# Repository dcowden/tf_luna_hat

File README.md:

# This is a hat for an orange pi 5, v1.2, that exposes the uarts and can bus from the headers.

## Setting up the orange pi image

These high level steps are needed:

* Install arm overlays to enable uart 3 and 4
* disable serial gettys on the tty ports for these
* install i2c tools

## unpolished stuff I did
sudo apt update
sudo apt install -y \
  make build-essential libssl-dev zlib1g-dev \
  libbz2-dev libreadline-dev libsqlite3-dev \
  wget curl llvm libncurses5-dev libncursesw5-dev \
  xz-utils tk-dev libffi-dev liblzma-dev python3-pip git

# Install pyenv
curl https://pyenv.run | bash

# Add pyenv to your shell
echo 'export PATH="$HOME/.pyenv/bin:$PATH"' >> ~/.bashrc
echo 'eval "$(pyenv init -)"' >> ~/.bashrc
echo 'eval "$(pyenv virtualenv-init -)"' >> ~/.bashrc
source ~/.bashrc

# Install a specific Python version, e.g. 3.11.9
pyenv install 3.11.9

# Set it as the default for your user
pyenv global 3.11.9

# Verify
python --version
apt install i2c-tools

for b in 0 1 2 3 4 5 6 7 9 10; do echo "=== /dev/i2c-$b ==="; i2cdetect -y $b; done

pyenv virtualenv 3.11.9 i2c
pyenv activate
pyenv install smbus2

sudo usermod -aG i2c $USER
echo 'KERNEL=="i2c-[0-9]*", GROUP="i2c", MODE="0660"' | sudo tee /etc/udev/rules.d/99-i2c.rules
sudo udevadm control --reload-rules
sudo udevadm trigger
newgrp i2c

systemctl status serial-getty@ttyS4.service
# disable if active:
sudo systemctl disable --now serial-getty@ttyS4.service
sudo systemctl mask serial-getty@ttyS4.service
systemctl status serial-getty@ttyS4.service
# disable if active:
sudo systemctl disable --now serial-getty@ttyS3.service
sudo systemctl mask serial-getty@ttyS3.service

u-boot-update

RESULTING SITUATION
root@ubuntu:~# ls -l /lib/firmware/6.1.0-1025-rockchip/device-tree/rockchip/overlay/i2c*
-rw-r--r-- 1 root root 414 Sep  6 23:28 /lib/firmware/6.1.0-1025-rockchip/device-tree/rockchip/overlay/i2c-1.dtbo
-rw-r--r-- 1 root root 414 Sep  6 23:28 /lib/firmware/6.1.0-1025-rockchip/device-tree/rockchip/overlay/i2c-3.dtbo
-rw-r--r-- 1 root root 414 Sep  6 23:28 /lib/firmware/6.1.0-1025-rockchip/device-tree/rockchip/overlay/i2c-5.dtbo
root@ubuntu:~# ls -l /lib/firmware/device-tree/rockchip/overlay/
total 12
-rw-r--r-- 1 root root 414 Sep  6 22:15 i2c-1.dtbo
-rw-r--r-- 1 root root 414 Sep  6 22:15 i2c-3.dtbo
-rw-r--r-- 1 root root 414 Sep  6 22:15 i2c-5.dtbo
root@ubuntu:~# cat /etc/default/u-boot
## /etc/default/u-boot - configuration file for u-boot-update(8)

U_BOOT_UPDATE="true"

#U_BOOT_ALTERNATIVES="default recovery"
#U_BOOT_DEFAULT="l0"
#U_BOOT_PROMPT="1"
#U_BOOT_ENTRIES="all"
#U_BOOT_MENU_LABEL="Debian GNU/Linux"
#U_BOOT_PARAMETERS="ro earlycon"
#U_BOOT_ROOT=""
#U_BOOT_TIMEOUT="50"
U_BOOT_FDT="device-tree/rockchip/rk3588s-orangepi-5.dtb"
U_BOOT_FDT_DIR="/lib/firmware/"
U_BOOT_FDT_OVERLAYS="device-tree/rockchip/overlay/i2c-1.dtbo device-tree/rockchip/overlay/i2c-5.dtbo device-tree/rockchip/overlay/i2c-3.dtbo"
#U_BOOT_FDT_OVERLAYS_DIR="device-tree/rockchip/overlay"
#U_BOOT_SYNC_DTBS="false"
root@ubuntu:~# cat /boot/extlinux/extlinux.conf
## /boot/extlinux/extlinux.conf
##
## IMPORTANT WARNING
##
## The configuration of this file is generated automatically.
## Do not edit this file manually, use: u-boot-update

default l0
menu title U-Boot menu
prompt 1
timeout 20

label l0
        menu label Ubuntu 24.04.1 LTS 6.1.0-1025-rockchip
        linux /boot/vmlinuz-6.1.0-1025-rockchip
        initrd /boot/initrd.img-6.1.0-1025-rockchip
        fdt /lib/firmware/6.1.0-1025-rockchip/device-tree/rockchip/rk3588s-orangepi-5.dtb
        fdtoverlays  /lib/firmware/6.1.0-1025-rockchip/device-tree/rockchip/overlay/i2c-1.dtbo /lib/firmware/6.1.0-1025-rockchip/device-tree/rockchip/overlay/i2c-5.dtbo /lib/firmware/6.1.0-1025-rockchip/device-tree/rockchip/overlay/i2c-3.dtbo
        append root=UUID=cb911622-d31a-45b1-be03-e6467c1b7637 rootwait rw console=ttyS2,1500000 console=tty1 cgroup_enable=cpuset cgroup_memory=1 cgroup_enable=memory

label l0r
        menu label Ubuntu 24.04.1 LTS 6.1.0-1025-rockchip (rescue target)
        linux /boot/vmlinuz-6.1.0-1025-rockchip
        initrd /boot/initrd.img-6.1.0-1025-rockchip
        fdt /lib/firmware/6.1.0-1025-rockchip/device-tree/rockchip/rk3588s-orangepi-5.dtb
        append root=UUID=cb911622-d31a-45b1-be03-e6467c1b7637 rootwait rw console=ttyS2,1500000 console=tty1 cgroup_enable=cpuset cgroup_memory=1 cgroup_enable=memory single

root@ubuntu:~# nano /etc/default/u-boot
root@ubuntu:~# root@ubuntu:~# u-boot-update
P: Checking for EXTLINUX directory... found.
P: Writing config for vmlinuz-6.1.0-1025-rockchip...
P: Updating /boot/extlinux/extlinux.conf...
root@ubuntu:~# cat /etc/default/u-boot
## /etc/default/u-boot - configuration file for u-boot-update(8)

U_BOOT_UPDATE="true"

#U_BOOT_ALTERNATIVES="default recovery"
#U_BOOT_DEFAULT="l0"
#U_BOOT_PROMPT="1"
#U_BOOT_ENTRIES="all"
#U_BOOT_MENU_LABEL="Debian GNU/Linux"
#U_BOOT_PARAMETERS="ro earlycon"
#U_BOOT_ROOT=""
#U_BOOT_TIMEOUT="50"
U_BOOT_FDT="device-tree/rockchip/rk3588s-orangepi-5.dtb"
U_BOOT_FDT_DIR="/lib/firmware/"
#U_BOOT_FDT_OVERLAYS="device-tree/rockchip/overlay/i2c-1.dtbo device-tree/rockchip/overlay/i2c-5.dtbo device-tree/rockchip/overlay/i2c-3.dtbo"
#U_BOOT_FDT_OVERLAYS="device-tree/rockchip/overlay/i2c-1.dtbo"
U_BOOT_FDT_OVERLAYS="device-tree/rockchip/overlay/rk3588-uart4-m0.dtbo device-tree/rockchip/overlay/rk3568-uart3-m0.dtbo"
#U_BOOT_FDT_OVERLAYS_DIR="device-tree/rockchip/overlay"
#U_BOOT_SYNC_DTBS="false"
root@ubuntu:~# cat /boot/extlinux/extlinux.conf
## /boot/extlinux/extlinux.conf
##
## IMPORTANT WARNING
##
## The configuration of this file is generated automatically.
## Do not edit this file manually, use: u-boot-update

default l0
menu title U-Boot menu
prompt 1
timeout 20

label l0
        menu label Ubuntu 24.04.1 LTS 6.1.0-1025-rockchip
        linux /boot/vmlinuz-6.1.0-1025-rockchip
        initrd /boot/initrd.img-6.1.0-1025-rockchip
        fdt /lib/firmware/6.1.0-1025-rockchip/device-tree/rockchip/rk3588s-orangepi-5.dtb
        fdtoverlays  /lib/firmware/6.1.0-1025-rockchip/device-tree/rockchip/overlay/rk3588-uart4-m0.dtbo /lib/firmware/6.1.0-1025-rockchip/device-tree/rockchip/overlay/rk3568-uart3-m0.dtbo
        append root=UUID=cb911622-d31a-45b1-be03-e6467c1b7637 rootwait rw console=ttyS2,1500000 console=tty1 cgroup_enable=cpuset cgroup_memory=1 cgroup_enable=memory

label l0r
        menu label Ubuntu 24.04.1 LTS 6.1.0-1025-rockchip (rescue target)
        linux /boot/vmlinuz-6.1.0-1025-rockchip
        initrd /boot/initrd.img-6.1.0-1025-rockchip
        fdt /lib/firmware/6.1.0-1025-rockchip/device-tree/rockchip/rk3588s-orangepi-5.dtb
        append root=UUID=cb911622-d31a-45b1-be03-e6467c1b7637 rootwait rw console=ttyS2,1500000 console=tty1 cgroup_enable=cpuset cgroup_memory=1 cgroup_enable=memory single

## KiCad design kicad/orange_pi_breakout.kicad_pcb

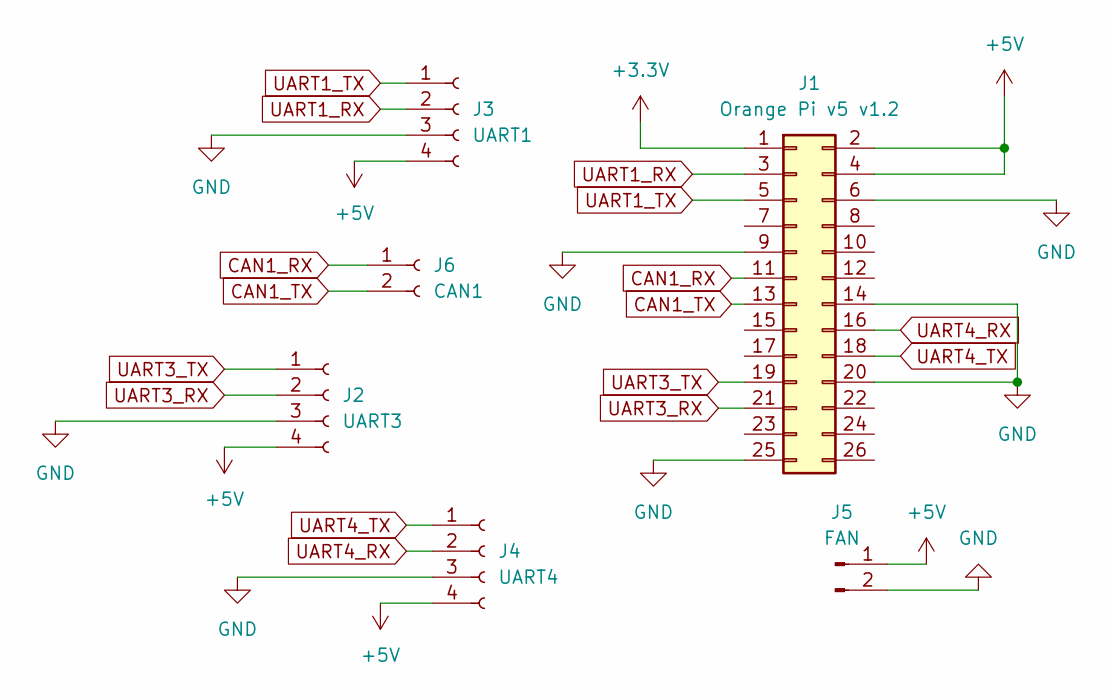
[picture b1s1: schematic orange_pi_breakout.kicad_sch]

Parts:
J1: Orange Pi v5 v1.2; PinSocket_2x13_P2.54mm_Vertical
J2: UART3; JST_XH_B4B-XH-A_1x04_P2.50mm_Vertical
J3: UART1; JST_XH_B4B-XH-A_1x04_P2.50mm_Vertical
J4: UART4; JST_XH_B4B-XH-A_1x04_P2.50mm_Vertical
J5: FAN; PinHeader_1x02_P2.54mm_Horizontal
J6: CAN1; JST_XH_B2B-XH-A_1x02_P2.50mm_Vertical

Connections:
+3.3V: J1.1
+5V: J1.2, J1.4, J2.4, J3.4, J4.4, J5.1
CAN1_RX: J1.11, J6.1
CAN1_TX: J1.13, J6.2
GND: J1.6, J1.9, J1.14, J1.20, J1.25, J2.3, J3.3, J4.3, J5.2
UART1_RX: J1.3, J3.2
UART1_TX: J1.5, J3.1
UART3_RX: J1.21, J2.2
UART3_TX: J1.19, J2.1
UART4_RX: J1.16, J4.2
UART4_TX: J1.18, J4.1

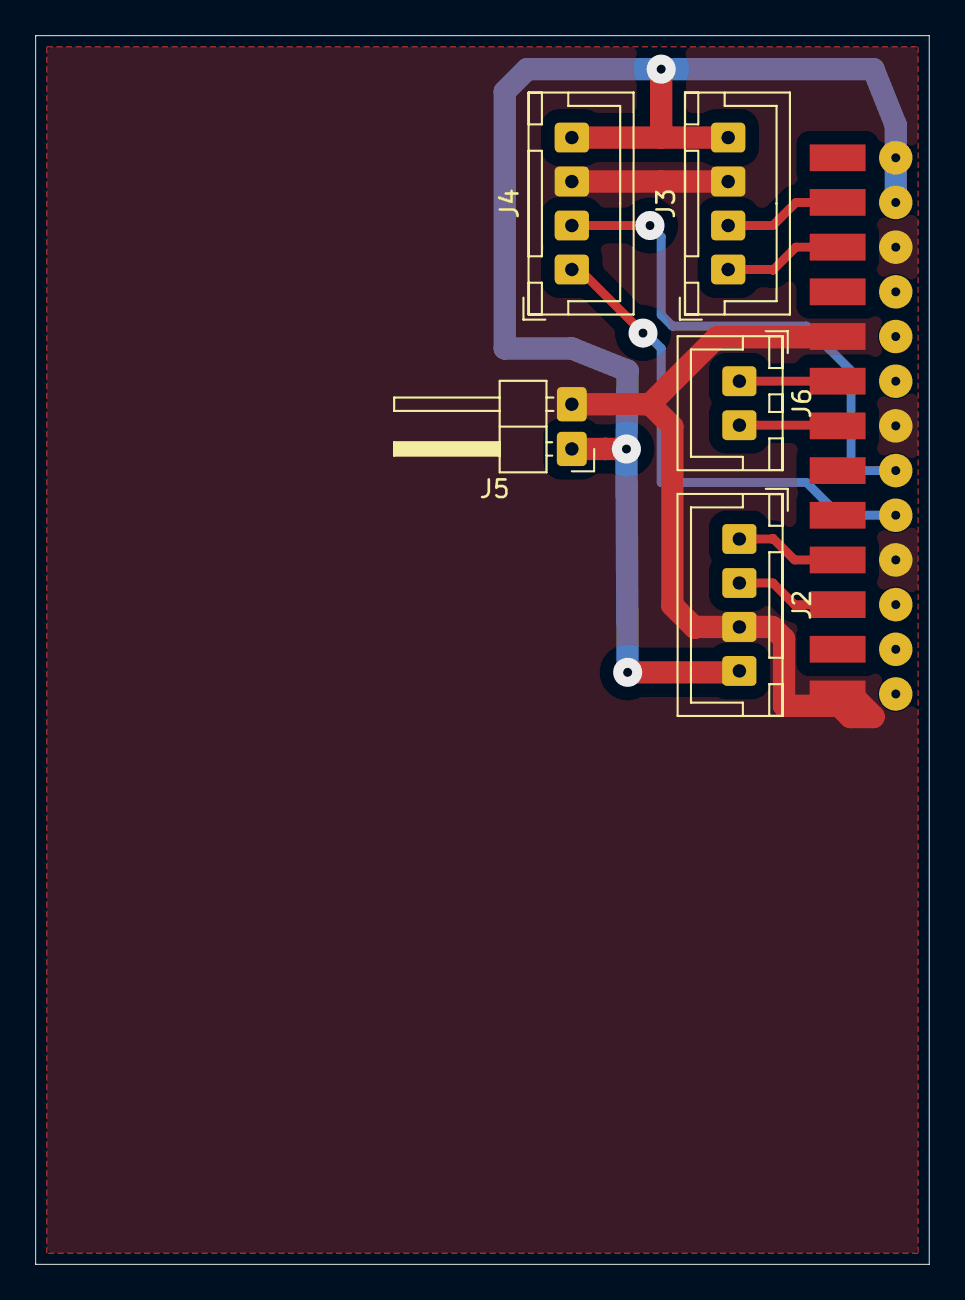
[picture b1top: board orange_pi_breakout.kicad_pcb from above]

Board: 2 copper layers, 50.8 x 69.8 mm, 6 parts (1 on the bottom side), 10 nets.
